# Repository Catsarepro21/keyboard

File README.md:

# KEEB

Its a custom keyboard! My current keyboard is pretty bad, and I thought why not make one, so i designed it.

KEEB is an 80-key keyboard built around a Pico W, with USB and Bluetooth, a rechargeable battery, a volume encoder, and an OLED. It has a custom PCB and a 3D printed case with the switch plate built into the top. RGB only works when plugged into USB, which I think is fine.

## Pictures

Renders (Blender + Onshape):

The case and integrated switch plate:

The full PCB layout:

A closer look at the routing around the Pico W and controls:

The OLED and encoder area:

The schematic (open the image to zoom in):

## Project files

- [BOM and purchasing links](BOM.md) · [CSV](BOM.csv)
- [Case STEP with integrated switch plate](cad/KEEB-case.step)
- [Onshape source CAD and complete keyboard assembly](https://cad.onshape.com/documents/a273834a75c8cf83eaf3eccf/w/175ac2f63e3c24ffd6632dd1/e/d788e341cf0c23216b358283)
- [KiCad project](pcb/keeb_pcb.kicad_pro)
- [KiCanvas view](https://kicanvas.org/?repo=https%3A%2F%2Fgithub.com%2FCatsarepro21%2Fkeyboard%2Ftree%2Fmain%2Fpcb)
- [Gerbers and drill files](fabrication/KEEB-gerbers.zip)
- [Firmware source](firmware/) · [UF2](firmware/KEEB.uf2)

If Onshape shows 403 when opened from GitHub for some reason, copy and paste this address into your browser:

```text
https://cad.onshape.com/documents/a273834a75c8cf83eaf3eccf/w/175ac2f63e3c24ffd6632dd1/e/d788e341cf0c23216b358283
```

## Wiring

The switches, diodes, encoder, and RGB are connected through the PCB. The OLED uses its included cable, with the board-side plug trimmed off and the four wires soldered directly to J1. Match the signal labels, since wire colors and connector order can vary.

```text
PCB J1                         OLED
1  GND ----------------------- GND
2  +3V3 ---------------------- VCC
3  OLED_SCL (Pico GP21) ------- SCL / CLK
4  OLED_SDA (Pico GP22) ------- SDA / DIN

Protected 500 mAh LiPo -------- JST_1 battery connector
                               Check + and - before plugging it in.
```

The OLED is the Waveshare 0.91 inch SSD1306 module, using I2C at address 0x3c. Use the PCB pad numbers above, not the order the wires happen to come in.

## How to assemble

1. Order the PCB using the Gerbers, and get the parts in the BOM below. The board is 359.95 x 124.25 mm, 2 layers, and 1.6 mm thick.
2. Import the case STEP into your slicer/CAD tool and export the three separate parts for printing: the bottom, top with integrated switch plate, and battery cover. Check the switch and stabilizer fit before committing to the full assembly.
3. Install the M3 heat-set inserts in the printed mounting holes. Let them cool before fitting the screws.
4. With USB and the battery disconnected, solder the small PCB components first: resistors, capacitors, diodes, power circuitry, and RGB LEDs. Follow the component references and orientations in KiCad, especially diode polarity, LED orientation, and IC pin 1.
5. Solder the battery connector, power switch, encoder, and Pico W mounting pins. Fit the Pico W in the orientation shown on the PCB, with its USB port lined up with the case opening.
6. Fit the PCB screw-in stabilizers before installing the switches. Clip the switches into the top's integrated plate, line their pins up with the PCB, and solder them. Check for bent pins as you go.
7. Wire the OLED as shown above and position it behind the case opening. Keep the cable clear of the switches and screw holes.
8. Check the solder joints for bridges and check for a short between power and ground. Leave the battery disconnected for the first USB test, then flash the firmware using the steps below.
9. Test every key, the encoder, and the OLED before closing the case. The current firmware sets the LEDs to dim blue when USB is configured.
10. Disconnect USB, check the battery connector polarity, and connect the protected LiPo. Secure and insulate it with the polyimide tape, keeping it clear of sharp pins and screws. Test battery power and Bluetooth before closing it up.
11. Fit the assembly into the bottom, route the OLED wires so they aren't pinched, and fasten the case and battery cover with the M3 screws. Add the keycaps, encoder knob, and four feet.

## How to flash

Use the included firmware for the original Pico W (RP2040).

1. Download [KEEB.uf2](firmware/KEEB.uf2) using GitHub's download button, or use the file from a downloaded copy of this repo.
2. Disconnect the battery and unplug USB.
3. Hold the Pico W's BOOTSEL button while connecting it to your computer with a USB data cable, then release the button.
4. A drive called `RPI-RP2` should show up. Copy `KEEB.uf2` onto it.
5. The Pico should restart and the drive should disappear. Check that the keyboard is detected, then try the keys in a text editor.

The firmware uses RMK, with the keymap in [keyboard.toml](firmware/keyboard.toml). The encoder is mapped to volume up/down, and its push switch is mapped to mute. Vial support is enabled for changing mappings over USB.

For Bluetooth, disconnect USB, connect the battery, turn on the power switch, and look for `KEEB Wireless` in your computer's Bluetooth pairing menu.

The OLED code displays `KEEB` and `USB` or `BAT`. `BAT` means battery mode, not a battery percentage. RGB and charging are enabled by the current firmware after the USB connection is configured.

## What I learned

Helped a lot with large PCB design, wiring carefully, and just overall laying things out well. Adding Bluetooth also meant adding a battery and charger, rerouting around the antenna area, and changing the case to fit everything.

## BOM

Original listed parts and PCB total: **$106.13**, with printing still to be priced. Check current prices and shipping before ordering.

| Part | Specification | Needed | Buy | Line cost | Link |
|---|---|---:|---:|---:|---|
| Wireless controller | Raspberry Pi SC0918 Pico W | 1 | 1 | $6.00 | [Buy](https://www.adafruit.com/product/5526) |
| MX key switches | Gateron KS-3Y10B050NW-X1 | 80 | 80 | $16.00 | [Buy](https://mechanicalkeyboards.com/products/gateron-milky-yellow-50g-linear) |
| Matrix diodes | XCH 1N4148 / C7437620 | 81 | 100 | $0.91 | [Buy](https://www.lcsc.com/product-detail/C7437620.html) |
| RGB LEDs | OPSCO SK6812MINI-E / C5149201 | 79 | 85 | $5.53 | [Buy](https://www.lcsc.com/product-detail/C5149201.html) |
| Rotary encoder with push | Alps EC11E18244AU | 1 | 1 | $2.22 | [Buy](https://www.lcsc.com/product-detail/C202365.html) |
| Battery charger | MCP73831T-2ACI/OT | 1 | 1 | $0.78 | [Buy](https://www.lcsc.com/product-detail/C424093.html) |
| Battery isolation diode | Vishay SS14-E3/61T | 1 | 3 | $0.35 | [Buy](https://www.lcsc.com/product-detail/C47460.html) |
| Power slide switch | Wurth 450301014042, 300 mA / 24 V DC | 1 | 1 | $2.15 | [Buy](https://www.digikey.com/en/products/detail/w%C3%BCrth-elektronik/450301014042/5209104) |
| Battery connector | JST B2B-PH-K-S(LF)(SN) | 1 | 20 | $0.71 | [Buy](https://www.lcsc.com/product-detail/C131337.html) |
| Charge-current resistor | Yageo RC0805FR-0710KL (10k, 0805) | 1 | 100 | $0.58 | [Buy](https://www.lcsc.com/product-detail/C84376.html) |
| Charger capacitors | TDK C2012X5R1V106MT000E / C415295 (10uF, 0805) | 2 | 2 | $0.52 | [Buy](https://www.lcsc.com/product-detail/C415295.html) |
| RGB data translator | TI SN74LVC1T45DBVR | 1 | 5 | $0.42 | [Buy](https://www.lcsc.com/product-detail/C7843.html) |
| RGB current limiter | TI TPS2553DBVR | 1 | 1 | $0.54 | [Buy](https://www.lcsc.com/product-detail/C55266.html) |
| Control/status expander | TI PCA9536DR | 1 | 1 | $1.56 | [Buy](https://www.digikey.com/en/products/detail/texas-instruments/PCA9536DR/1573050) |
| Charger load switch | TI TPS22918DBVR | 1 | 1 | $0.59 | [Buy](https://www.digikey.com/en/products/detail/texas-instruments/TPS22918DBVR/5994601) |
| USB detection MOSFET | onsemi BSS138LT1G | 1 | 10 | $0.44 | [Buy](https://www.lcsc.com/product-detail/C82045.html) |
| Local bypass capacitors | Samsung CL10B104KB8NNNC (100nF, 0603) | 82 | 100 | $0.82 | [Buy](https://www.lcsc.com/product-detail/C1591.html) |
| USB switch input capacitors | Samsung CL21B105KAFNNNE (1uF, 0805) | 2 | 10 | $0.41 | [Buy](https://www.lcsc.com/product-detail/C116352.html) |
| RGB bulk capacitor | Samsung CL31A226KAHNNNE (22uF, 1206) | 1 | 1 | $0.48 | [Buy](https://www.digikey.com/en/products/detail/samsung-electro-mechanics/CL31A226KAHNNNE/3888705) |
| Charger rise-time capacitor | Murata GRM1885C1H103JA01D (10nF, 0603) | 1 | 1 | $0.14 | [Buy](https://www.digikey.com/en/products/detail/murata-electronics/GRM1885C1H103JA01D/4934772) |
| 330 ohm LED data series | Yageo RC0603FR-07330RL (330, 0603) | 1 | 10 | $0.25 | [Buy](https://www.digikey.com/en/products/detail/yageo/RC0603FR-07330RL/727162) |
| 100 kohm RGB pull-downs | Yageo RC0603FR-07100KL (100k, 0603) | 2 | 10 | $0.25 | [Buy](https://www.digikey.com/en/products/detail/yageo/RC0603FR-07100KL/729836) |
| 2.2 kohm enables and VBUS bleed | Yageo RC0603FR-072K2L (2.2k, 0603) | 3 | 100 | $0.18 | [Buy](https://www.lcsc.com/product-detail/C114662.html) |
| 4.7 kohm I2C pull-ups to 3.3 V | Yageo RC0603FR-074K7L (4.7k, 0603) | 2 | 10 | $0.25 | [Buy](https://www.digikey.com/en/products/detail/yageo/RC0603FR-074K7L/727212) |
| 10 kohm status pull-ups | Yageo RC0603FR-0710KL (10k, 0603) | 2 | 100 | $0.34 | [Buy](https://www.lcsc.com/product-detail/C98220.html) |
| 160 kohm RGB current limit | Yageo RC0603FR-07160KL (160k, 0603) | 1 | 100 | $0.22 | [Buy](https://www.lcsc.com/product-detail/C137793.html) |
| OLED board-side connection | Included cable: trim plug and direct-solder four wires by signal; no header | 1 | 1 | $0.00 | [Buy](https://www.waveshare.com/product/ai/0.91inch-oled-module.htm) |
| Stabilizer kit | Fynmi black PCB screw-in kit, 4 x 2u + 1 x 6.25u | 5 | 1 | $4.09 | [Buy](https://www.aliexpress.us/item/3256810601892072.html) |
| Protected LiPo battery | Adafruit 1578, 500 mAh | 1 | 1 | $7.95 | [Buy](https://www.adafruit.com/product/1578) |
| OLED module | Waveshare 14657, SSD1306 128 x 32 | 1 | 1 | $6.99 | [Buy](https://www.waveshare.com/product/ai/0.91inch-oled-module.htm) |
| Encoder knob | Adafruit 5093 | 1 | 1 | $0.75 | [Buy](https://www.adafruit.com/product/5093) |
| USB data cable | Cvilux DH-20M50055 | 1 | 1 | $1.58 | [Buy](https://www.digikey.com/en/products/detail/cvilux-usa/DH-20M50055/13175849) |
| Keycap set | 129-key white pudding PBT, OEM profile, MX stems; required key sizes covered | 80 | 1 | $10.22 | [Buy](https://www.aliexpress.us/item/3256809062215921.html) |
| Case inserts | XHHD SZTB1150 / C51939019, M3 x 4.5 x 5 mm | 10 | 20 | $0.47 | [Buy](https://www.lcsc.com/product-detail/C51939019.html) |
| Case screws | M3 50pcs / 8mm ISO7380 button-head | 10 | 50 | $1.75 | [Buy](https://www.aliexpress.us/item/3256801950414714.html) |
| Adhesive feet | Adafruit 550, pack of four approx 8 × 4 mm bumpers | 4 | 1 | $0.95 | [Buy](https://www.adafruit.com/product/550) |
| Case print | Printed bottom, top with integrated MX switch plate, removable battery cover | 3 | 1 | Printing Legion? | [Buy](https://printlegion.hackclub.com/) |
| Controller mounting pins | BOOMELE 2.54-1*40P / C2337 | 1 | 5 | $0.80 | [Buy](https://www.lcsc.com/product-detail/C2337.html) |
| Battery retention/insulation | JSZ-007 polyimide tape, 30 mm x 33 m x 0.05 mm | 1 | 1 | $2.34 | [Buy](https://www.lcsc.com/product-detail/C6798411.html) |
| PCB | 359.95 x 124.25 mm; 2 layers; 1.6 mm FR4; green; HASL; no optional paid production-file confirmation | 1 | 5 | $25.60 | [Buy](https://jlcpcb.com/quote) |
| AliExpress shipping | White keycaps and Fynmi stabilizers together; cart showed free shipping on 13 October 2026 | 1 | 1 | $0.00 | [Buy](https://www.aliexpress.us/p/shoppingcart/index.html) |

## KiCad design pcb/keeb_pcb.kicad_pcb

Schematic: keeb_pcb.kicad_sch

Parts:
A1: Raspberry Pi Pico W; RaspberryPi_Pico_Common_THT_Bare_W
C1, C2: 10uF; C_0805_2012Metric
C3, C4, C5, C101, C102, C103, C104, C105, C106, C107, C108, C109, C110, C111, C112, C113, C114, C115, C116, C117, C118, C119, C120, C121, C122, C123, C124, C125, C126, C127, C128, C129, C130, C131, C132, C133, C134, C135, C136, C137, C138, C139, C140, C141, C142, C143, C144, C145, C146, C147, C148, C149, C150, C151, C152, C153, C154, C155, C156, C157, C158, C159, C160, C161, C162, C163, C164, C165, C166, C167, C168, C169, C170, C171, C172, C173, C174, C175, C176, C177, C178, C179: 100nF; C_0603_1608Metric
C6, C10: 1uF; C_0805_2012Metric
C7: 22uF; C_1206_3216Metric
C9: 10nF; C_0603_1608Metric
D1: SS14; D_SMA
D2, D3, D4, D5, D6, D7, D8, D9, D10, D11, D12, D13, D14, D15, D16, D17, D18, D19, D20, D21, D22, D23, D24, D25, D26, D27, D28, D29, D30, D31, D32, D33, D34, D35, D36, D37, D38, D39, D40, D41, D42, D43, D44, D45, D46, D47, D48, D49, D50, D51, D52, D53, D54, D55, D57, D58, D60, D61, D62, D63, D64, D65, D66, D67, D68, D69, D71, D72, D73, D74, D77, D79, D80, D81, D82, D90, D91, D92, D93, D94, D95: 1N4148; D_DO-35_SOD27_P7.62mm_Horizontal
ENC1: EC11; RotaryEncoder_Alps_EC11E-Switch_Vertical_H20mm
J1: Conn_01x04; PinHeader_1x04_P2.54mm_Vertical
JST_1: J_BAT; JST_PH_B2B-PH-K_1x02_P2.00mm_Vertical
Q2: BSS138LT1G; SOT-23
R1: 10k; R_0805_2012Metric
R2: 330; R_0603_1608Metric
R3, R4: 100k; R_0603_1608Metric
R5, R6, R10: 2.2k; R_0603_1608Metric
R7, R8: 4.7k; R_0603_1608Metric
R9, R11: 10k; R_0603_1608Metric
R12: 160k; R_0603_1608Metric
RGB1, RGB2, RGB3, RGB4, RGB5, RGB6, RGB7, RGB8, RGB9, RGB10, RGB11, RGB12, RGB13, RGB14, RGB15, RGB16, RGB17, RGB18, RGB19, RGB20, RGB21, RGB22, RGB23, RGB24, RGB25, RGB26, RGB27, RGB31, RGB32, RGB33, RGB34, RGB35, RGB36, RGB37, RGB38, RGB39, RGB40, RGB41, RGB42, RGB43, RGB46, RGB47, RGB48, RGB49, RGB50, RGB51, RGB52, RGB53, RGB54, RGB55, RGB56, RGB57, RGB58, RGB59, RGB60, RGB61, RGB62, RGB63, RGB64, RGB65, RGB66, RGB67, RGB68, RGB69, RGB70, RGB71, RGB72, RGB73, RGB74, RGB75, RGB76, RGB77, RGB78, RGB79, RGB80, RGB81, RGB82, RGB83, RGB84: SK6812MINI-E; LED_SK6812MINI-E_3.2x2.8mm_P1.5mm_ReverseMount
S1, S3, S4, S7: MX_stab; STAB_MX_2u
S8: MX_stab_6.25u; STAB_MX_6.25u
SW1: SW_PWR; SW_Slide-03_Wuerth-WS-SLTV_10x2.5x6.4_P2.54mm
SW2, SW3, SW4, SW5, SW6, SW7, SW8, SW9, SW10, SW11, SW13, SW14, SW15, SW16, SW17, SW18, SW19, SW20, SW21, SW22, SW23, SW24, SW25, SW26, SW27, SW29, SW30, SW31, SW32, SW33, SW34, SW35, SW36, SW37, SW38, SW39, SW40, SW41, SW42, SW43, SW44, SW45, SW46, SW47, SW48, SW49, SW50, SW51, SW52, SW53, SW54, SW55, SW57, SW58, SW60, SW61, SW62, SW63, SW64, SW65, SW66, SW67, SW68, SW69, SW71, SW72, SW73, SW74, SW77, SW79, SW80, SW81, SW82, SW90, SW91, SW92, SW93: SW_Push; SW_MX_1u
SW12: SW_Push; SW_MX_1u_RGB_Clearance
SW94: Programmable 1; SW_MX_1u
SW95: Programmable 2; SW_MX_1u
U1: MCP73831-2-OT; SOT-23-5
U2: SN74LVC1T45DBVR; SOT-23-6
U3: TPS2553DBVR; SOT-23-6
U4: PCA9536DR; SOIC-8_3.9x4.9mm_P1.27mm
U5: TPS22918DBVR; SOT-23-6

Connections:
+3V3: A1.36 (3V3), C3.1, C5.1, J1.2, R7.1, R8.1, R9.1, R11.1, U2.1 (VCCA), U2.5 (DIR), U4.8 (VCC)
+5V: A1.40 (VBUS), C6.1, C10.1, Q2.1 (G), R10.1, U3.1 (IN), U5.1 (VIN)
/BAT+: C2.2, JST_1.1, SW1.2 (B), U1.3 (V_{BAT})
/BAT_SW: D1.2 (A), SW1.1 (A)
/CHG_PROG: R1.2, U1.5 (PROG)
/COL0: A1.9 (GPIO6), SW2.1, SW16.1, SW30.1, SW44.1, SW58.1, SW72.1
/COL1: A1.10 (GPIO7), SW3.1, SW17.1, SW31.1, SW45.1, SW73.1
/COL2: A1.11 (GPIO8), SW4.1, SW18.1, SW32.1, SW46.1, SW60.1, SW74.1
/COL3: A1.12 (GPIO9), SW5.1, SW19.1, SW33.1, SW47.1, SW61.1, SW91.1
/COL4: A1.14 (GPIO10), SW6.1, SW20.1, SW34.1, SW48.1, SW62.1, SW92.1
/COL5: A1.15 (GPIO11), SW7.1, SW21.1, SW35.1, SW49.1, SW63.1, SW94.1
/COL6: A1.16 (GPIO12), SW8.1, SW22.1, SW36.1, SW50.1, SW64.1, SW95.1
/COL7: A1.17 (GPIO13), SW9.1, SW23.1, SW37.1, SW51.1, SW65.1, SW77.1
/COL8: A1.19 (GPIO14), SW10.1, SW24.1, SW38.1, SW52.1, SW66.1
/COL9: A1.20 (GPIO15), SW11.1, SW25.1, SW39.1, SW53.1, SW67.1
/COL10: A1.21 (GPIO16), SW12.1, SW26.1, SW40.1, SW54.1, SW68.1, SW79.1
/COL11: A1.22 (GPIO17), SW13.1, SW27.1, SW41.1, SW55.1, SW69.1, SW80.1
/COL12: A1.24 (GPIO18), SW14.1, SW42.1, SW81.1
/COL13: A1.25 (GPIO19), SW15.1, SW29.1, SW43.1, SW57.1, SW71.1, SW82.1
/COL14: A1.26 (GPIO20), ENC1.S2, SW90.1, SW93.1
/OLED_SCL: A1.27 (GPIO21), J1.3, R7.2, U4.6 (SCL)
/OLED_SDA: A1.29 (GPIO22), J1.4, R8.2, U4.7 (SDA)
/ROW0: A1.1 (GPIO0), D2.1 (K), D3.1 (K), D4.1 (K), D5.1 (K), D6.1 (K), D7.1 (K), D8.1 (K), D9.1 (K), D10.1 (K), D11.1 (K), D12.1 (K), D13.1 (K), D14.1 (K), D15.1 (K), D28.1 (K)
/ROW1: A1.2 (GPIO1), D16.1 (K), D17.1 (K), D18.1 (K), D19.1 (K), D20.1 (K), D21.1 (K), D22.1 (K), D23.1 (K), D24.1 (K), D25.1 (K), D26.1 (K), D27.1 (K), D29.1 (K)
/ROW2: A1.4 (GPIO2), D30.1 (K), D31.1 (K), D32.1 (K), D33.1 (K), D34.1 (K), D35.1 (K), D36.1 (K), D37.1 (K), D38.1 (K), D39.1 (K), D40.1 (K), D41.1 (K), D42.1 (K), D43.1 (K)
/ROW3: A1.5 (GPIO3), D44.1 (K), D45.1 (K), D46.1 (K), D47.1 (K), D48.1 (K), D49.1 (K), D50.1 (K), D51.1 (K), D52.1 (K), D53.1 (K), D54.1 (K), D55.1 (K), D57.1 (K)
/ROW4: A1.6 (GPIO4), D58.1 (K), D60.1 (K), D61.1 (K), D62.1 (K), D63.1 (K), D64.1 (K), D65.1 (K), D66.1 (K), D67.1 (K), D68.1 (K), D69.1 (K), D71.1 (K), D90.1 (K)
/ROW5: A1.7 (GPIO5), D72.1 (K), D73.1 (K), D74.1 (K), D77.1 (K), D79.1 (K), D80.1 (K), D81.1 (K), D82.1 (K), D91.1 (K), D92.1 (K), D93.1 (K), D94.1 (K), D95.1 (K)
CHG_5V: C1.1, U1.4 (V_{DD}), U5.5 (QOD), U5.6 (VOUT)
CHG_ENABLE: R6.1, U4.2 (IO1), U5.3 (ON)
CHG_SLEW: C9.1, U5.4 (CT)
ENC1_A: A1.32 (GPIO27_ADC1), ENC1.A
ENC1_B: A1.34 (GPIO28_ADC2), ENC1.B
GND: A1.3 (GND), A1.8 (GND), A1.13 (GND), A1.18 (GND), A1.23 (GND), A1.28 (GND), A1.38 (GND), C1.2, C2.1, C3.2, C4.2, C5.2, C6.2, C7.2, C9.2, C10.2, C101.2, C102.2, C103.2, C104.2, C105.2, C106.2, C107.2, C108.2, C109.2, C110.2, C111.2, C112.2, C113.2, C114.2, C115.2, C116.2, C117.2, C118.2, C119.2, C120.2, C121.2, C122.2, C123.2, C124.2, C125.2, C126.2, C127.2, C128.2, C129.2, C130.2, C131.2, C132.2, C133.2, C134.2, C135.2, C136.2, C137.2, C138.2, C139.2, C140.2, C141.2, C142.2, C143.2, C144.2, C145.2, C146.2, C147.2, C148.2, C149.2, C150.2, C151.2, C152.2, C153.2, C154.2, C155.2, C156.2, C157.2, C158.2, C159.2, C160.2, C161.2, C162.2, C163.2, C164.2, C165.2, C166.2, C167.2, C168.2, C169.2, C170.2, C171.2, C172.2, C173.2, C174.2, C175.2, C176.2, C177.2, C178.2, C179.2, ENC1.C, J1.1, JST_1.2, Q2.2 (S), R1.1, R3.2, R4.2, R5.2, R6.2, R10.2, R12.2, RGB1.1 (VSS), RGB2.1 (VSS), RGB3.1 (VSS), RGB4.1 (VSS), RGB5.1 (VSS), RGB6.1 (VSS), RGB7.1 (VSS), RGB8.1 (VSS), RGB9.1 (VSS), RGB10.1 (VSS), RGB11.1 (VSS), RGB12.1 (VSS), RGB13.1 (VSS), RGB14.1 (VSS), RGB15.1 (VSS), RGB16.1 (VSS), RGB17.1 (VSS), RGB18.1 (VSS), RGB19.1 (VSS), RGB20.1 (VSS), RGB21.1 (VSS), RGB22.1 (VSS), RGB23.1 (VSS), RGB24.1 (VSS), RGB25.1 (VSS), RGB26.1 (VSS), RGB27.1 (VSS), RGB31.1 (VSS), RGB32.1 (VSS), RGB33.1 (VSS), RGB34.1 (VSS), RGB35.1 (VSS), RGB36.1 (VSS), RGB37.1 (VSS), RGB38.1 (VSS), RGB39.1 (VSS), RGB40.1 (VSS), RGB41.1 (VSS), RGB42.1 (VSS), RGB43.1 (VSS), RGB46.1 (VSS), RGB47.1 (VSS), RGB48.1 (VSS), RGB49.1 (VSS), RGB50.1 (VSS), RGB51.1 (VSS), RGB52.1 (VSS), RGB53.1 (VSS), RGB54.1 (VSS), RGB55.1 (VSS), RGB56.1 (VSS), RGB57.1 (VSS), RGB58.1 (VSS), RGB59.1 (VSS), RGB60.1 (VSS), RGB61.1 (VSS), RGB62.1 (VSS), RGB63.1 (VSS), RGB64.1 (VSS), RGB65.1 (VSS), RGB66.1 (VSS), RGB67.1 (VSS), RGB68.1 (VSS), RGB69.1 (VSS), RGB70.1 (VSS), RGB71.1 (VSS), RGB72.1 (VSS), RGB73.1 (VSS), RGB74.1 (VSS), RGB75.1 (VSS), RGB76.1 (VSS), RGB77.1 (VSS), RGB78.1 (VSS), RGB79.1 (VSS), RGB80.1 (VSS), RGB81.1 (VSS), RGB82.1 (VSS), RGB83.1 (VSS), RGB84.1 (VSS), U1.2 (V_{SS}), U2.2 (GND), U3.2 (GND), U4.4 (GND), U5.2 (GND)
unnamed: A1.39 (VSYS), D1.1 (K)
unnamed: D2.2 (A), SW2.2
unnamed: D3.2 (A), SW3.2
unnamed: D4.2 (A), SW4.2
unnamed: D5.2 (A), SW5.2
unnamed: D6.2 (A), SW6.2
unnamed: D7.2 (A), SW7.2
unnamed: D8.2 (A), SW8.2
unnamed: D9.2 (A), SW9.2
unnamed: D10.2 (A), SW10.2
unnamed: D11.2 (A), SW11.2
unnamed: D12.2 (A), SW12.2
unnamed: D13.2 (A), SW13.2
unnamed: D14.2 (A), SW14.2
unnamed: D15.2 (A), SW15.2
unnamed: D16.2 (A), SW16.2
unnamed: D17.2 (A), SW17.2
unnamed: D18.2 (A), SW18.2
unnamed: D19.2 (A), SW19.2
unnamed: D20.2 (A), SW20.2
unnamed: D21.2 (A), SW21.2
unnamed: D22.2 (A), SW22.2
unnamed: D23.2 (A), SW23.2
unnamed: D24.2 (A), SW24.2
unnamed: D25.2 (A), SW25.2
unnamed: D26.2 (A), SW26.2
unnamed: D27.2 (A), SW27.2
unnamed: D28.2 (A), ENC1.S1
unnamed: D29.2 (A), SW29.2
unnamed: D30.2 (A), SW30.2
unnamed: D31.2 (A), SW31.2
unnamed: D32.2 (A), SW32.2
unnamed: D33.2 (A), SW33.2
unnamed: D34.2 (A), SW34.2
unnamed: D35.2 (A), SW35.2
unnamed: D36.2 (A), SW36.2
unnamed: D37.2 (A), SW37.2
unnamed: D38.2 (A), SW38.2
unnamed: D39.2 (A), SW39.2
unnamed: D40.2 (A), SW40.2
unnamed: D41.2 (A), SW41.2
unnamed: D42.2 (A), SW42.2
unnamed: D43.2 (A), SW43.2
unnamed: D44.2 (A), SW44.2
unnamed: D45.2 (A), SW45.2
unnamed: D46.2 (A), SW46.2
unnamed: D47.2 (A), SW47.2
unnamed: D48.2 (A), SW48.2
unnamed: D49.2 (A), SW49.2
unnamed: D50.2 (A), SW50.2
unnamed: D51.2 (A), SW51.2
unnamed: D52.2 (A), SW52.2
unnamed: D53.2 (A), SW53.2
unnamed: D54.2 (A), SW54.2
unnamed: D55.2 (A), SW55.2
unnamed: D57.2 (A), SW57.2
unnamed: D58.2 (A), SW58.2
unnamed: D60.2 (A), SW60.2
unnamed: D61.2 (A), SW61.2
unnamed: D62.2 (A), SW62.2
unnamed: D63.2 (A), SW63.2
unnamed: D64.2 (A), SW64.2
unnamed: D65.2 (A), SW65.2
unnamed: D66.2 (A), SW66.2
unnamed: D67.2 (A), SW67.2
unnamed: D68.2 (A), SW68.2
unnamed: D69.2 (A), SW69.2
unnamed: D71.2 (A), SW71.2
unnamed: D72.2 (A), SW72.2
unnamed: D73.2 (A), SW73.2
unnamed: D74.2 (A), SW74.2
unnamed: D77.2 (A), SW77.2
unnamed: D79.2 (A), SW79.2
unnamed: D80.2 (A), SW80.2
unnamed: D81.2 (A), SW81.2
unnamed: D82.2 (A), SW82.2
unnamed: D90.2 (A), SW90.2
unnamed: D91.2 (A), SW91.2
unnamed: D92.2 (A), SW92.2
unnamed: D93.2 (A), SW93.2
unnamed: D94.2 (A), SW94.2
unnamed: D95.2 (A), SW95.2
RGB_5V: C4.1, C7.1, C101.1, C102.1, C103.1, C104.1, C105.1, C106.1, C107.1, C108.1, C109.1, C110.1, C111.1, C112.1, C113.1, C114.1, C115.1, C116.1, C117.1, C118.1, C119.1, C120.1, C121.1, C122.1, C123.1, C124.1, C125.1, C126.1, C127.1, C128.1, C129.1, C130.1, C131.1, C132.1, C133.1, C134.1, C135.1, C136.1, C137.1, C138.1, C139.1, C140.1, C141.1, C142.1, C143.1, C144.1, C145.1, C146.1, C147.1, C148.1, C149.1, C150.1, C151.1, C152.1, C153.1, C154.1, C155.1, C156.1, C157.1, C158.1, C159.1, C160.1, C161.1, C162.1, C163.1, C164.1, C165.1, C166.1, C167.1, C168.1, C169.1, C170.1, C171.1, C172.1, C173.1, C174.1, C175.1, C176.1, C177.1, C178.1, C179.1, RGB1.3 (VDD), RGB2.3 (VDD), RGB3.3 (VDD), RGB4.3 (VDD), RGB5.3 (VDD), RGB6.3 (VDD), RGB7.3 (VDD), RGB8.3 (VDD), RGB9.3 (VDD), RGB10.3 (VDD), RGB11.3 (VDD), RGB12.3 (VDD), RGB13.3 (VDD), RGB14.3 (VDD), RGB15.3 (VDD), RGB16.3 (VDD), RGB17.3 (VDD), RGB18.3 (VDD), RGB19.3 (VDD), RGB20.3 (VDD), RGB21.3 (VDD), RGB22.3 (VDD), RGB23.3 (VDD), RGB24.3 (VDD), RGB25.3 (VDD), RGB26.3 (VDD), RGB27.3 (VDD), RGB31.3 (VDD), RGB32.3 (VDD), RGB33.3 (VDD), RGB34.3 (VDD), RGB35.3 (VDD), RGB36.3 (VDD), RGB37.3 (VDD), RGB38.3 (VDD), RGB39.3 (VDD), RGB40.3 (VDD), RGB41.3 (VDD), RGB42.3 (VDD), RGB43.3 (VDD), RGB46.3 (VDD), RGB47.3 (VDD), RGB48.3 (VDD), RGB49.3 (VDD), RGB50.3 (VDD), RGB51.3 (VDD), RGB52.3 (VDD), RGB53.3 (VDD), RGB54.3 (VDD), RGB55.3 (VDD), RGB56.3 (VDD), RGB57.3 (VDD), RGB58.3 (VDD), RGB59.3 (VDD), RGB60.3 (VDD), RGB61.3 (VDD), RGB62.3 (VDD), RGB63.3 (VDD), RGB64.3 (VDD), RGB65.3 (VDD), RGB66.3 (VDD), RGB67.3 (VDD), RGB68.3 (VDD), RGB69.3 (VDD), RGB70.3 (VDD), RGB71.3 (VDD), RGB72.3 (VDD), RGB73.3 (VDD), RGB74.3 (VDD), RGB75.3 (VDD), RGB76.3 (VDD), RGB77.3 (VDD), RGB78.3 (VDD), RGB79.3 (VDD), RGB80.3 (VDD), RGB81.3 (VDD), RGB82.3 (VDD), RGB83.3 (VDD), RGB84.3 (VDD), U2.6 (VCCB), U3.6 (OUT)
RGB_BUFFER_OUT: R2.1, U2.4 (B)
RGB_D1: RGB1.4 (DOUT), RGB2.2 (DIN)
RGB_D2: RGB2.4 (DOUT), RGB3.2 (DIN)
RGB_D3: RGB3.4 (DOUT), RGB4.2 (DIN)
RGB_D4: RGB4.4 (DOUT), RGB5.2 (DIN)
RGB_D5: RGB5.4 (DOUT), RGB6.2 (DIN)
RGB_D6: RGB6.4 (DOUT), RGB7.2 (DIN)
RGB_D7: RGB7.4 (DOUT), RGB8.2 (DIN)
RGB_D8: RGB8.4 (DOUT), RGB9.2 (DIN)
RGB_D9: RGB9.4 (DOUT), RGB10.2 (DIN)
RGB_D10: RGB10.4 (DOUT), RGB11.2 (DIN)
RGB_D11: RGB11.4 (DOUT), RGB12.2 (DIN)
RGB_D12: RGB12.4 (DOUT), RGB13.2 (DIN)
RGB_D13: RGB14.2 (DIN), RGB84.4 (DOUT)
RGB_D14: RGB14.4 (DOUT), RGB15.2 (DIN)
RGB_D15: RGB15.4 (DOUT), RGB16.2 (DIN)
RGB_D16: RGB16.4 (DOUT), RGB17.2 (DIN)
RGB_D17: RGB17.4 (DOUT), RGB18.2 (DIN)
RGB_D18: RGB18.4 (DOUT), RGB19.2 (DIN)
RGB_D19: RGB19.4 (DOUT), RGB20.2 (DIN)
RGB_D20: RGB20.4 (DOUT), RGB21.2 (DIN)
RGB_D21: RGB21.4 (DOUT), RGB22.2 (DIN)
RGB_D22: RGB22.4 (DOUT), RGB23.2 (DIN)
RGB_D23: RGB23.4 (DOUT), RGB24.2 (DIN)
RGB_D24: RGB24.4 (DOUT), RGB25.2 (DIN)
RGB_D25: RGB25.4 (DOUT), RGB26.2 (DIN)
RGB_D26: RGB26.4 (DOUT), RGB27.2 (DIN)
RGB_D27: RGB27.4 (DOUT), RGB31.2 (DIN)
RGB_D31: RGB31.4 (DOUT), RGB32.2 (DIN)
RGB_D32: RGB32.4 (DOUT), RGB33.2 (DIN)
RGB_D33: RGB33.4 (DOUT), RGB34.2 (DIN)
RGB_D34: RGB34.4 (DOUT), RGB35.2 (DIN)
RGB_D35: RGB35.4 (DOUT), RGB36.2 (DIN)
RGB_D36: RGB36.4 (DOUT), RGB37.2 (DIN)
RGB_D37: RGB37.4 (DOUT), RGB38.2 (DIN)
RGB_D38: RGB38.4 (DOUT), RGB39.2 (DIN)
RGB_D39: RGB39.4 (DOUT), RGB40.2 (DIN)
RGB_D40: RGB40.4 (DOUT), RGB41.2 (DIN)
RGB_D41: RGB41.4 (DOUT), RGB42.2 (DIN)
RGB_D42: RGB42.4 (DOUT), RGB43.2 (DIN)
RGB_D43: RGB43.4 (DOUT), RGB46.2 (DIN)
RGB_D46: RGB46.4 (DOUT), RGB47.2 (DIN)
RGB_D47: RGB47.4 (DOUT), RGB48.2 (DIN)
RGB_D48: RGB48.4 (DOUT), RGB49.2 (DIN)
RGB_D49: RGB49.4 (DOUT), RGB50.2 (DIN)
RGB_D50: RGB50.4 (DOUT), RGB51.2 (DIN)
RGB_D51: RGB51.4 (DOUT), RGB52.2 (DIN)
RGB_D52: RGB52.4 (DOUT), RGB53.2 (DIN)
RGB_D53: RGB53.4 (DOUT), RGB54.2 (DIN)
RGB_D54: RGB54.4 (DOUT), RGB55.2 (DIN)
RGB_D55: RGB55.4 (DOUT), RGB56.2 (DIN)
RGB_D56: RGB56.4 (DOUT), RGB57.2 (DIN)
RGB_D57: RGB57.4 (DOUT), RGB58.2 (DIN)
RGB_D58: RGB58.4 (DOUT), RGB59.2 (DIN)
RGB_D59: RGB59.4 (DOUT), RGB60.2 (DIN)
RGB_D60: RGB60.4 (DOUT), RGB61.2 (DIN)
RGB_D61: RGB61.4 (DOUT), RGB62.2 (DIN)
RGB_D62: RGB62.4 (DOUT), RGB63.2 (DIN)
RGB_D63: RGB63.4 (DOUT), RGB64.2 (DIN)
RGB_D64: RGB64.4 (DOUT), RGB65.2 (DIN)
RGB_D65: RGB65.4 (DOUT), RGB66.2 (DIN)
RGB_D66: RGB66.4 (DOUT), RGB67.2 (DIN)
RGB_D67: RGB67.4 (DOUT), RGB68.2 (DIN)
RGB_D68: RGB68.4 (DOUT), RGB69.2 (DIN)
RGB_D69: RGB69.4 (DOUT), RGB70.2 (DIN)
RGB_D70: RGB70.4 (DOUT), RGB71.2 (DIN)
RGB_D71: RGB71.4 (DOUT), RGB72.2 (DIN)
RGB_D72: RGB72.4 (DOUT), RGB73.2 (DIN)
RGB_D73: RGB73.4 (DOUT), RGB74.2 (DIN)
RGB_D74: RGB74.4 (DOUT), RGB75.2 (DIN)
RGB_D75: RGB75.4 (DOUT), RGB76.2 (DIN)
RGB_D76: RGB76.4 (DOUT), RGB77.2 (DIN)
RGB_D77: RGB77.4 (DOUT), RGB78.2 (DIN)
RGB_D78: RGB78.4 (DOUT), RGB79.2 (DIN)
RGB_D79: RGB79.4 (DOUT), RGB80.2 (DIN)
RGB_D80: RGB80.4 (DOUT), RGB81.2 (DIN)
RGB_D81: RGB81.4 (DOUT), RGB82.2 (DIN)
RGB_DATA: A1.31 (GPIO26_ADC0), R3.1, U2.3 (A)
RGB_DIN_5V: R2.2, R4.1, RGB1.2 (DIN)
RGB_ENABLE: R5.1, U3.3 (EN), U4.1 (IO0)
RGB_FAULT_N: R11.2, U3.4 (FAULT_N), U4.5 (IO3)
RGB_ILIM: R12.1, U3.5 (ILIM)
RGB_NEW_A: RGB13.4 (DOUT), RGB83.2 (DIN)
RGB_NEW_B: RGB83.4 (DOUT), RGB84.2 (DIN)
USB_PRESENT_N: Q2.3 (D), R9.2, U4.3 (IO2)

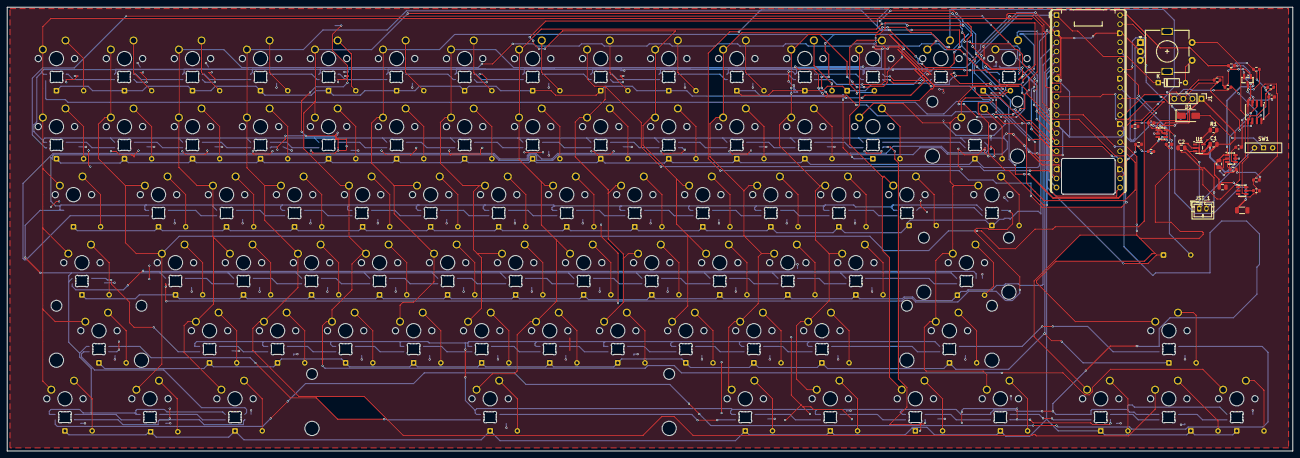
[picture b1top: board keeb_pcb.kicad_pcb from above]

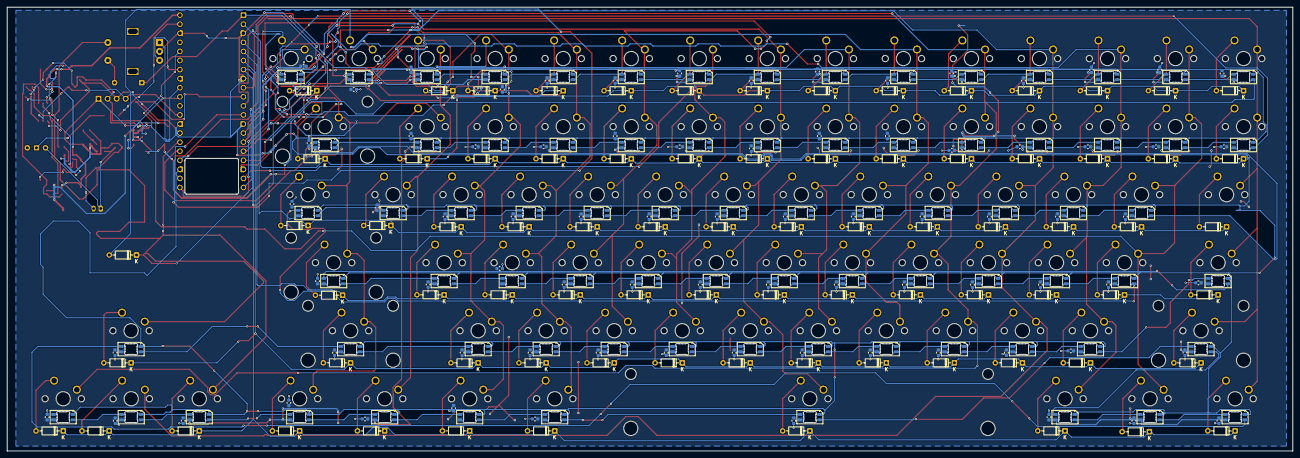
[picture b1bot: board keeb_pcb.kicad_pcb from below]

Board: 2 copper layers, 359.9 x 124.2 mm, 357 parts (238 on the bottom side), 202 nets.
